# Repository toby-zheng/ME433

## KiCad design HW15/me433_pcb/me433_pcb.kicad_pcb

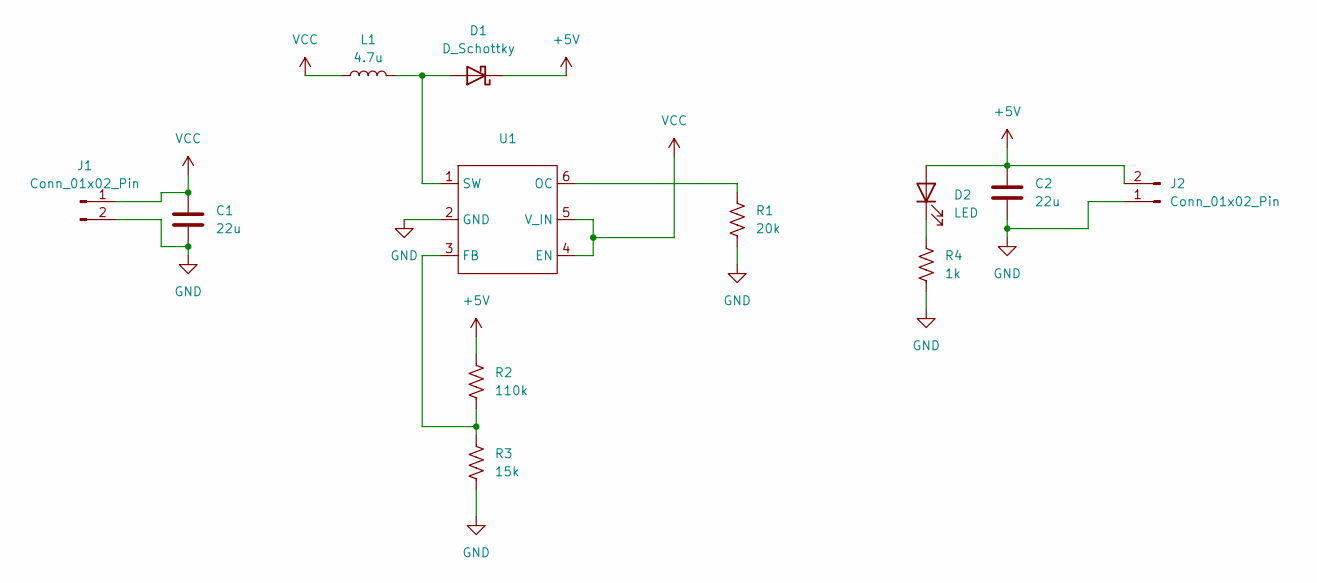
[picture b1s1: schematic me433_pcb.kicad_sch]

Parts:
C1, C2: 22u; C_0603_1608Metric_Pad1.08x0.95mm_HandSolder
D1: D_Schottky; D_SOD-123
D2: LED; LED_0603_1608Metric
J1, J2: Conn_01x02_Pin; PinHeader_1x02_P2.54mm_Vertical
L1: 4.7u; L_0805_2012Metric
R1: 20k; R_0805_2012Metric
R2: 110k; R_0805_2012Metric
R3: 15k; R_0805_2012Metric
R4: 1k; R_0805_2012Metric
U1: SOT-23-6

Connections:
+5V: C2.1, D1.1 (K), D2.2 (A), J2.2, R2.1
GND: C1.2, C2.2, J1.2, J2.1, R1.2, R3.2, R4.2, U1.2 (GND)
unnamed: D1.2 (A), L1.2, U1.1 (SW)
unnamed: D2.1 (K), R4.1
unnamed: R2.2, R3.1, U1.3 (FB)
unnamed: R1.1, U1.6 (OC)
VCC: C1.1, J1.1, L1.1, U1.4 (EN), U1.5 (V_IN)

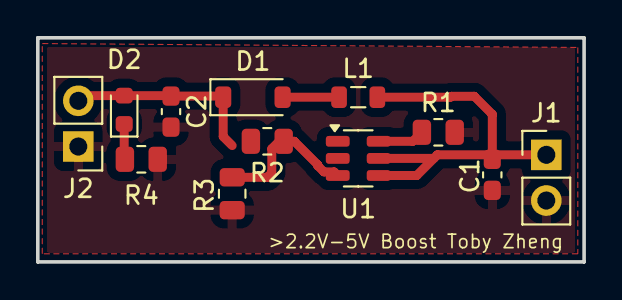
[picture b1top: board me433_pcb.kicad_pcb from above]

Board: 2 copper layers, 30.3 x 12.5 mm, 12 parts (0 on the bottom side), 7 nets.

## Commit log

2025-04-03 example code commit - also changed delay in blink to 1000ms
2025-04-03 CMakeLists.txt missing tinyusb
2025-04-03 homework2 code: - button press toggles GPIO25 LED - button press prints press count
2025-04-03 comments
2025-04-03 fixed small issue w/ counter iterating -1
2025-04-08 homework 3
2025-04-08 video for homework3
2025-04-11 verified DAC control, implemented data manipulation such that function calls are easier
2025-04-12 hw4 code and image
2025-04-17 fpu test
2025-04-17 fpu corrected
2025-04-17 screenshot
2025-04-22 Homework 6-- IO Expander w/ LED
2025-04-22 Video via upload
2025-04-24 homework 7
2025-04-24 video for hw7
2025-05-01 hw 8
2025-05-01 homework 8
2025-05-01 HW8 video
2025-05-06 hw9 + video
2025-05-11 hw10
2025-05-15 hw11
2025-05-22 hw15
2025-05-22 hw12
2025-06-01 hw13 -- imu
2025-06-02 hw12 updated
2025-06-02 HW14
2025-06-04 hw16
